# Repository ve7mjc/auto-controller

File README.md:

# auto-controller
Embedded Automation Controller for Automobiles.  Provides a number of powerful and flexible aftermarket functionality.

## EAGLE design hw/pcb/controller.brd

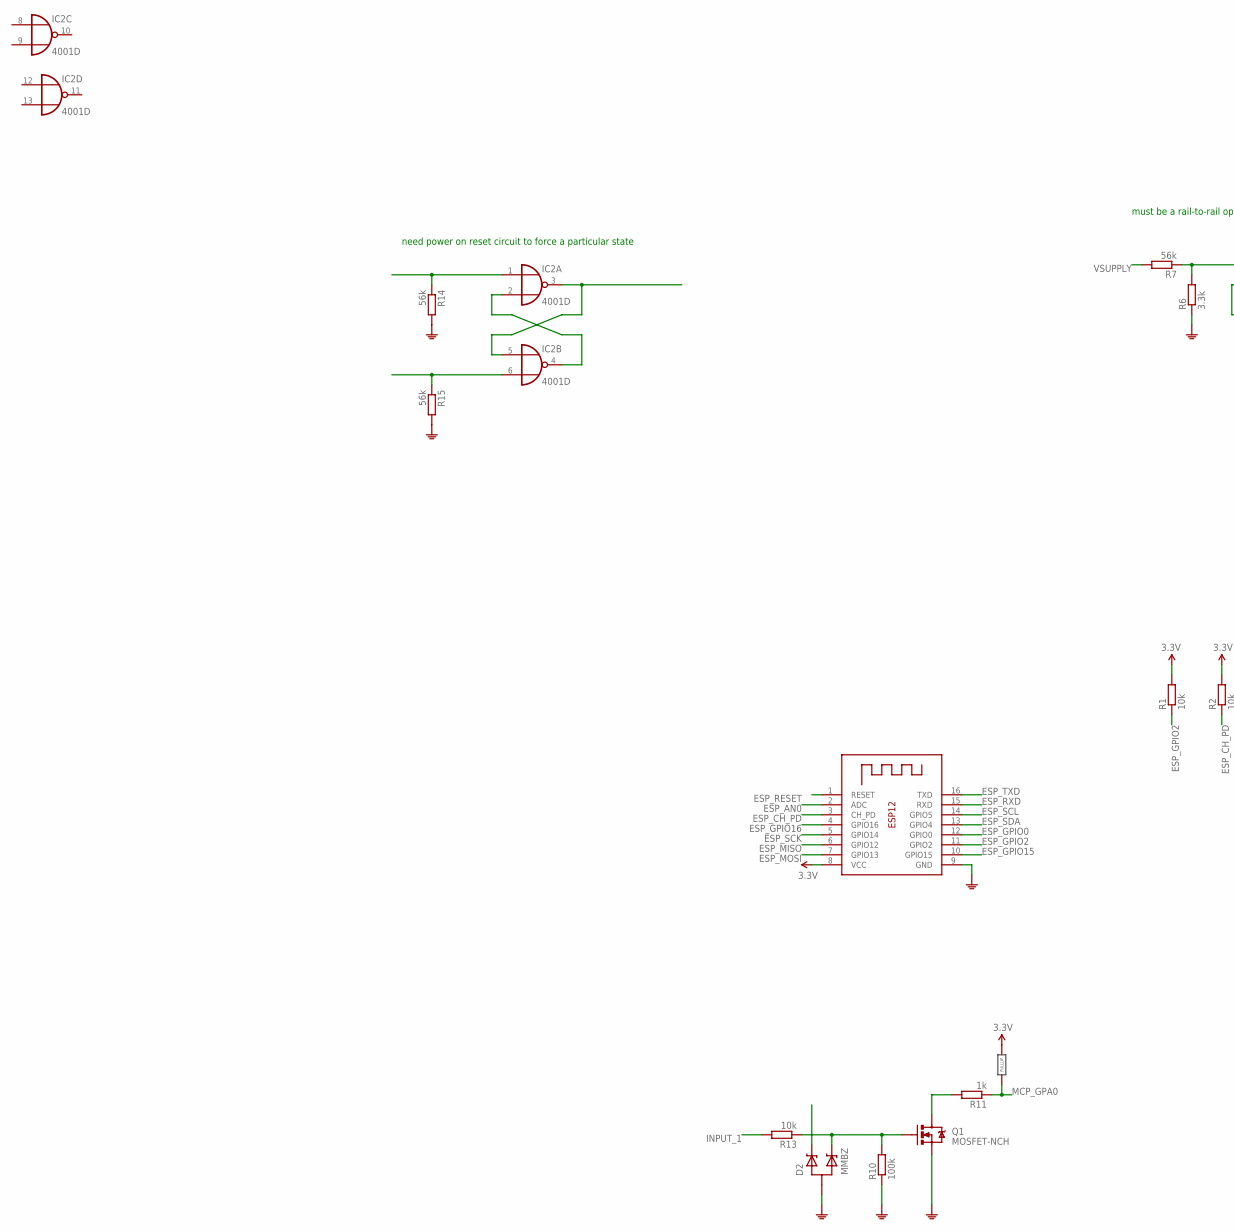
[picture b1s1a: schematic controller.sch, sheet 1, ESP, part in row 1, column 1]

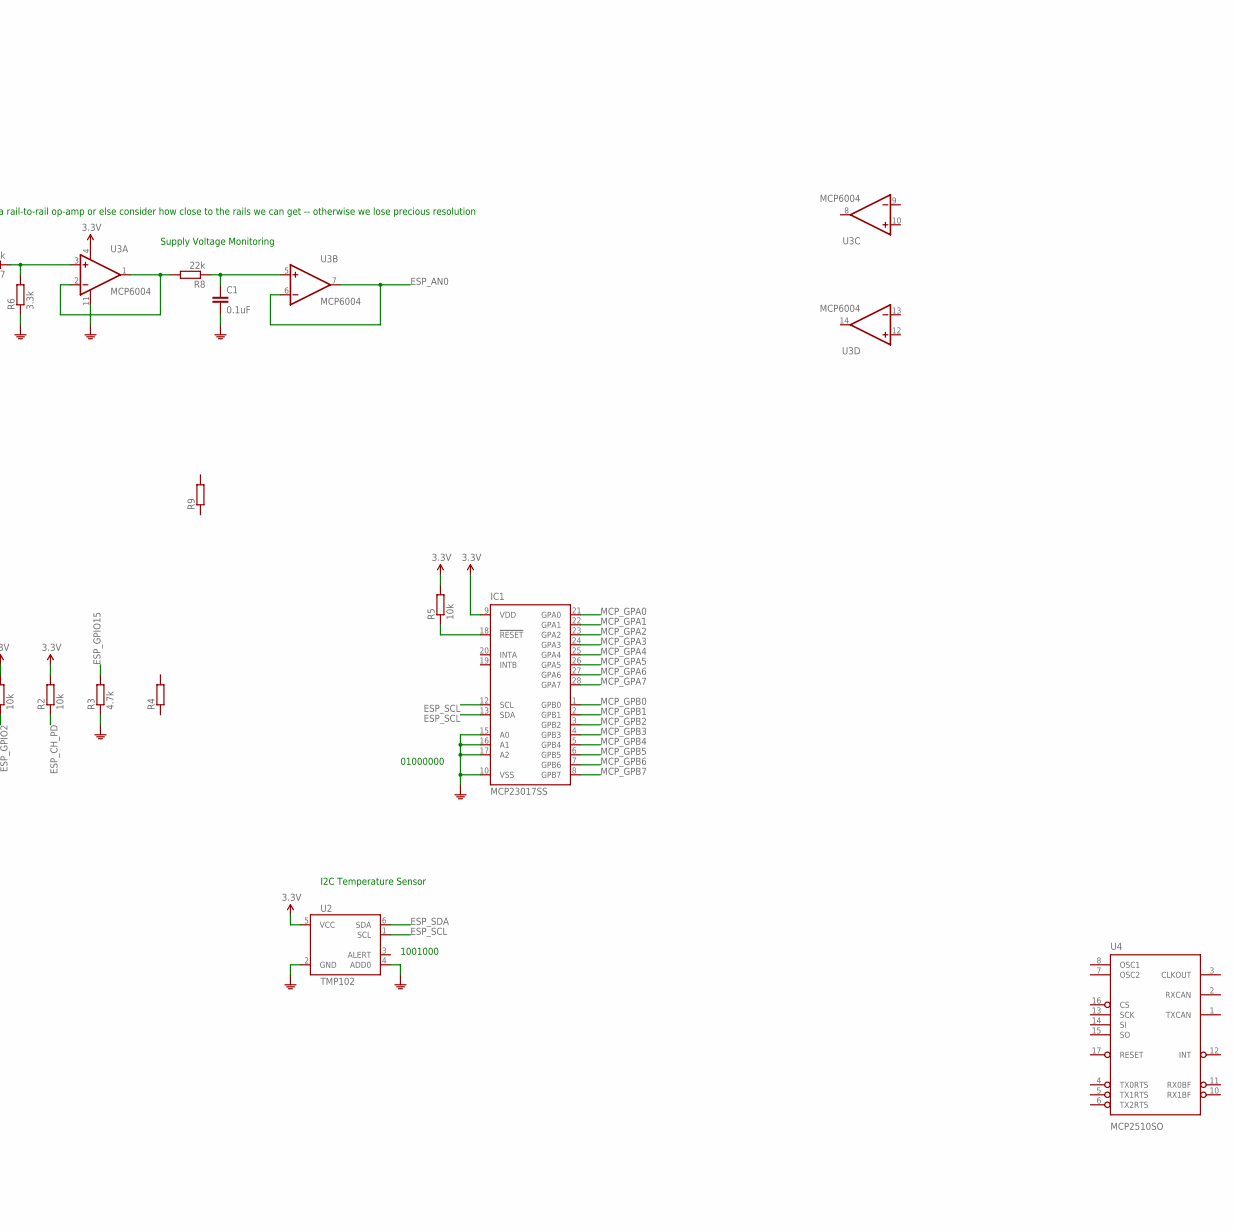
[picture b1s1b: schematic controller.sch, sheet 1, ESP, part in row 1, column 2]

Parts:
C1: 0.1uF; C0603K
D2: MMBZ; SOT23
IC1: MCP23017SS; SSOP28
IC2: 4001D; SO14
Q1: MOSFET-NCH; SOT23-3
R1, R2, R5, R13: 10k; R0603
R3: 4.7k; R0603
R4, R9: R-EU_R0603; R0603
R6: 3.3k; R0603
R7, R14, R15: 56k; R0603
R8: 22k; R0603
R10: 100k; R0603
R11: 1k; R0603
U2: TMP102; SOT563
U3: MCP6004; TSSOP_14
U4: MCP2510SO; SO-18W
X1: ESP-12

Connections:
3.3V: IC1.9 (VDD), R1.2, R2.2, R5.2, U2.5 (VCC), U3.4 (V+), X1.8 (VCC)
ESP_AN0: U3.6 (-IN), U3.7 (OUT), X1.2 (ADC)
ESP_CH_PD: R2.1, X1.3 (CH_PD)
ESP_GPIO0: X1.12 (GPIO0)
ESP_GPIO2: R1.1, X1.11 (GPIO2)
ESP_GPIO15: R3.2, X1.10 (GPIO15)
ESP_GPIO16: X1.4 (GPIO16)
ESP_MISO: X1.6 (GPIO12)
ESP_MOSI: X1.7 (GPIO13)
ESP_RESET: X1.1 (RESET)
ESP_RXD: X1.15 (RXD)
ESP_SCK: X1.5 (GPIO14)
ESP_SCL: IC1.12 (SCL), IC1.13 (SDA), U2.1 (SCL), X1.14 (GPIO5)
ESP_SDA: U2.6 (SDA), X1.13 (GPIO4)
ESP_TXD: X1.16 (TXD)
GND: C1.2, D2.3 (ANODE), IC1.10 (VSS), IC1.15 (A0), IC1.16 (A1), IC1.17 (A2), Q1.2 (S), R3.1, R6.1, R10.1, R14.2, R15.2, U2.2 (GND), U2.4 (ADD0), U3.11 (V-), X1.9 (GND); also elsewhere on the board
INPUT_1: R13.2; also elsewhere on the board
INPUT_ACCESSORY: D2.2 (CATHODE_2), Q1.1 (G), R10.2, R13.1; also elsewhere on the board
MCP_GPA0: IC1.21 (GPA0), R11.1
MCP_GPA1: IC1.22 (GPA1)
MCP_GPA2: IC1.23 (GPA2)
MCP_GPA3: IC1.24 (GPA3)
MCP_GPA4: IC1.25 (GPA4)
MCP_GPA5: IC1.26 (GPA5)
MCP_GPA6: IC1.27 (GPA6)
MCP_GPA7: IC1.28 (GPA7)
MCP_GPB0: IC1.1 (GPB0)
MCP_GPB1: IC1.2 (GPB1)
MCP_GPB2: IC1.3 (GPB2)
MCP_GPB3: IC1.4 (GPB3)
MCP_GPB4: IC1.5 (GPB4)
MCP_GPB5: IC1.6 (GPB5)
MCP_GPB6: IC1.7 (GPB6)
MCP_GPB7: IC1.8 (GPB7)
unnamed: IC1.18 (!RESET), R5.1
unnamed: R6.2, R7.1, U3.3 (+IN)
unnamed: R8.2, U3.1 (OUT), U3.2 (-IN)
unnamed: C1.1, R8.1, U3.5 (+IN)
unnamed: Q1.3 (D), R11.2
unnamed: IC2.3 (O), IC2.5 (I0)
unnamed: IC2.1 (I0), R14.1
unnamed: IC2.6 (I1), R15.1
unnamed: IC2.2 (I1), IC2.4 (O)
VDD: IC2.14 (VDD), U4.18 (VDD)
VSS: IC2.7 (VSS), U4.9 (VSS)
VSUPPLY: R7.2; also elsewhere on the board

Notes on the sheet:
1001000
I2C Temperature Sensor
01000000
Supply Voltage Monitoring
must be a rail-to-rail op-amp or else consider how close to the rails we can get -- otherwise we lose precious resolution
need power on reset circuit to force a particular state

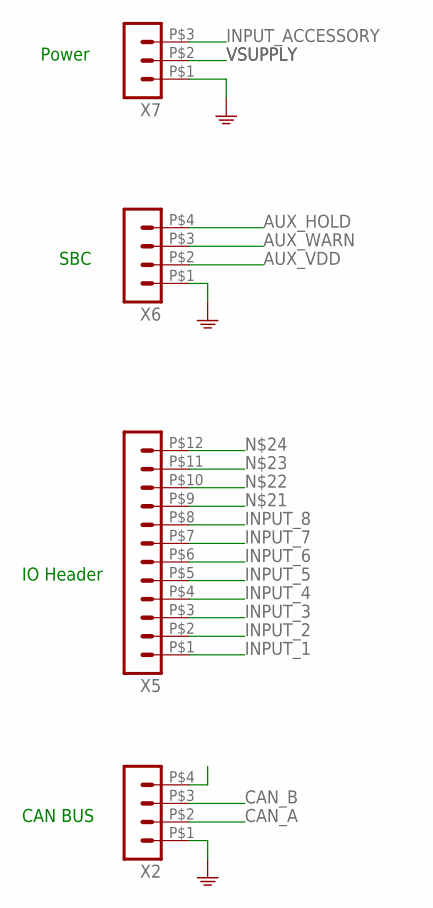
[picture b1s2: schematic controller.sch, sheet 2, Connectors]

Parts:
X2, X6: HEADER_POS4_43045-0401; 43045-0400
X5: HEADER_POS12_43045-1200; 43045-1200
X7: HEADER_POS3_43650-0300; 43650-0300

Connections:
AUX_HOLD: X6.P$4 (4)
AUX_VDD: X6.P$2 (2)
AUX_WARN: X6.P$3 (3)
CAN_A: X2.P$2 (2)
CAN_B: X2.P$3 (3)
GND: X2.P$1 (1), X6.P$1 (1), X7.P$1 (1); also elsewhere on the board
INPUT_1: X5.P$1 (1); also elsewhere on the board
INPUT_2: X5.P$2 (2)
INPUT_3: X5.P$3 (3)
INPUT_4: X5.P$4 (4)
INPUT_5: X5.P$5 (5)
INPUT_6: X5.P$6 (6)
INPUT_7: X5.P$7 (7)
INPUT_8: X5.P$8 (8)
INPUT_ACCESSORY: X7.P$3 (3); also elsewhere on the board
VSUPPLY: X7.P$2 (2); also elsewhere on the board

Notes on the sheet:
Power
SBC
IO Header
CAN BUS

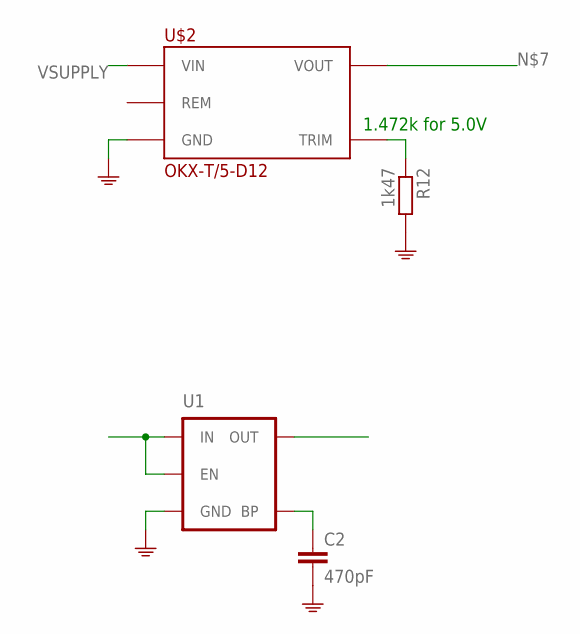
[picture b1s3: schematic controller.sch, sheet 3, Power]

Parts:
C2: 470pF; R0603
R12: 1k47; R0603
U1: MIC52053.3V; SOT23-5
U$2: OKX-T/5-D12; OKX_SIP

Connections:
GND: C2.2, R12.2, U1.2 (GND), U$2.P$3 (GND); also elsewhere on the board
unnamed: R12.1, U$2.P$2 (TRIM)
unnamed: U1.1 (IN), U1.3 (EN)
unnamed: C2.1, U1.4 (BP)
VSUPPLY: U$2.P$4 (VIN); also elsewhere on the board

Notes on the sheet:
1.472k for 5.0V

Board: 2 copper layers, 31 parts (0 on the bottom side), 26 nets, no tracks yet.

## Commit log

2016-01-28 working aux control over mqtt; working multi-input and inversion

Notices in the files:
parts and their libraries:
SparkFun-PowerIC: Licensing: Creative Commons ShareAlike 4.0 International - https://creativecommons.org/licenses/by-sa/4.0
SparkFun: Licensing: CC v3.0 Share-Alike You are welcome to use this library for commercial purposes.
